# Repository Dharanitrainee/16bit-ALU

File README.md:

<h1>16-bit ALU with ESP32 Control Unit</h1>

<p>This project implements a 16-bit Arithmetic Logic Unit (ALU) using TTL (74 series) digital integrated circuits. The control unit is built using an ESP32 microcontroller, enhancing functionality with a user-friendly interface via an OLED display and a rotary encoder for selecting operations.</p>

<blockquote>
  <strong>Disclaimer</strong>: This is my first PCB design, and there may be flaws.This may be the worls worst ALU!. Any feedback or suggestions for improvement are welcome.
</blockquote>

<h2>Features</h2>

<ul>
  <li><strong>Arithmetic Operations</strong>: Addition, Subtraction, Increment, Decrement.</li>
  <li><strong>Logical Operations</strong>: AND, OR, XOR, NOT.</li>
  <li><strong>User Interface</strong>: An OLED display shows the current operation, and a rotary encoder allows for easy selection of operations.</li>
  <li><strong>Control Mechanism</strong>: ESP32 provides control signals and manages data flow within the ALU using shift registers.</li>
</ul>

<h2>Components Used</h2>

<ul>
  <li><strong>TTL ICs (74 series)</strong> for logic implementation</li>
  <li><strong>ESP32 microcontroller</strong> for control signals</li>
  <li><strong>OLED Display (SH1106)</strong> for displaying selected operation and result</li>
  <li><strong>Rotary Encoder (KY-040)</strong> for operation selection</li>
  <li><strong>Shift Registers (74HC595)</strong> for handling input/output</li>
</ul>

<h2>Project Structure</h2>

<ul>
  <li><code>main_code.ino</code>: The primary Arduino code for the ESP32, managing the control signals, encoder input, OLED output, and ALU operations.</li>
  <li><code>images/</code>: Contains bitmaps for icons representing each operation.</li>
  <li><code>README.md</code>: Project documentation.</li>
</ul>

<h2>How It Works</h2>

<ol>
  <li><strong>Control Unit</strong>: The ESP32 microcontroller generates control signals based on user input from the rotary encoder. The OLED screen displays the current operation, input values, and results.</li>
  <li><strong>ALU Operations</strong>: The ALU performs selected operations on 16-bit data, interfaced via shift registers.</li>
  <li><strong>Result Display</strong>: The result of the operation is shown on the OLED display.</li>
</ol>

<h2>Setup and Usage</h2>

<ol>
  <li>Connect the ESP32 to the OLED display and rotary encoder.</li>
  <li>Interface the shift registers with TTL ICs to implement the 16-bit ALU logic.</li>
  <li>Load the Arduino code onto the ESP32.</li>
  <li>Use the rotary encoder to select the desired operation and input values, then view the result on the OLED display.</li>
</ol>

<h2>Future Improvements</h2>

<ul>
  <li>Expand operations to include multiplication and division.</li>
  <li>Optimize the control signal generation for improved speed and accuracy.</li>
  <li>Add support for additional user inputs or controls to expand functionality.</li>
</ul>

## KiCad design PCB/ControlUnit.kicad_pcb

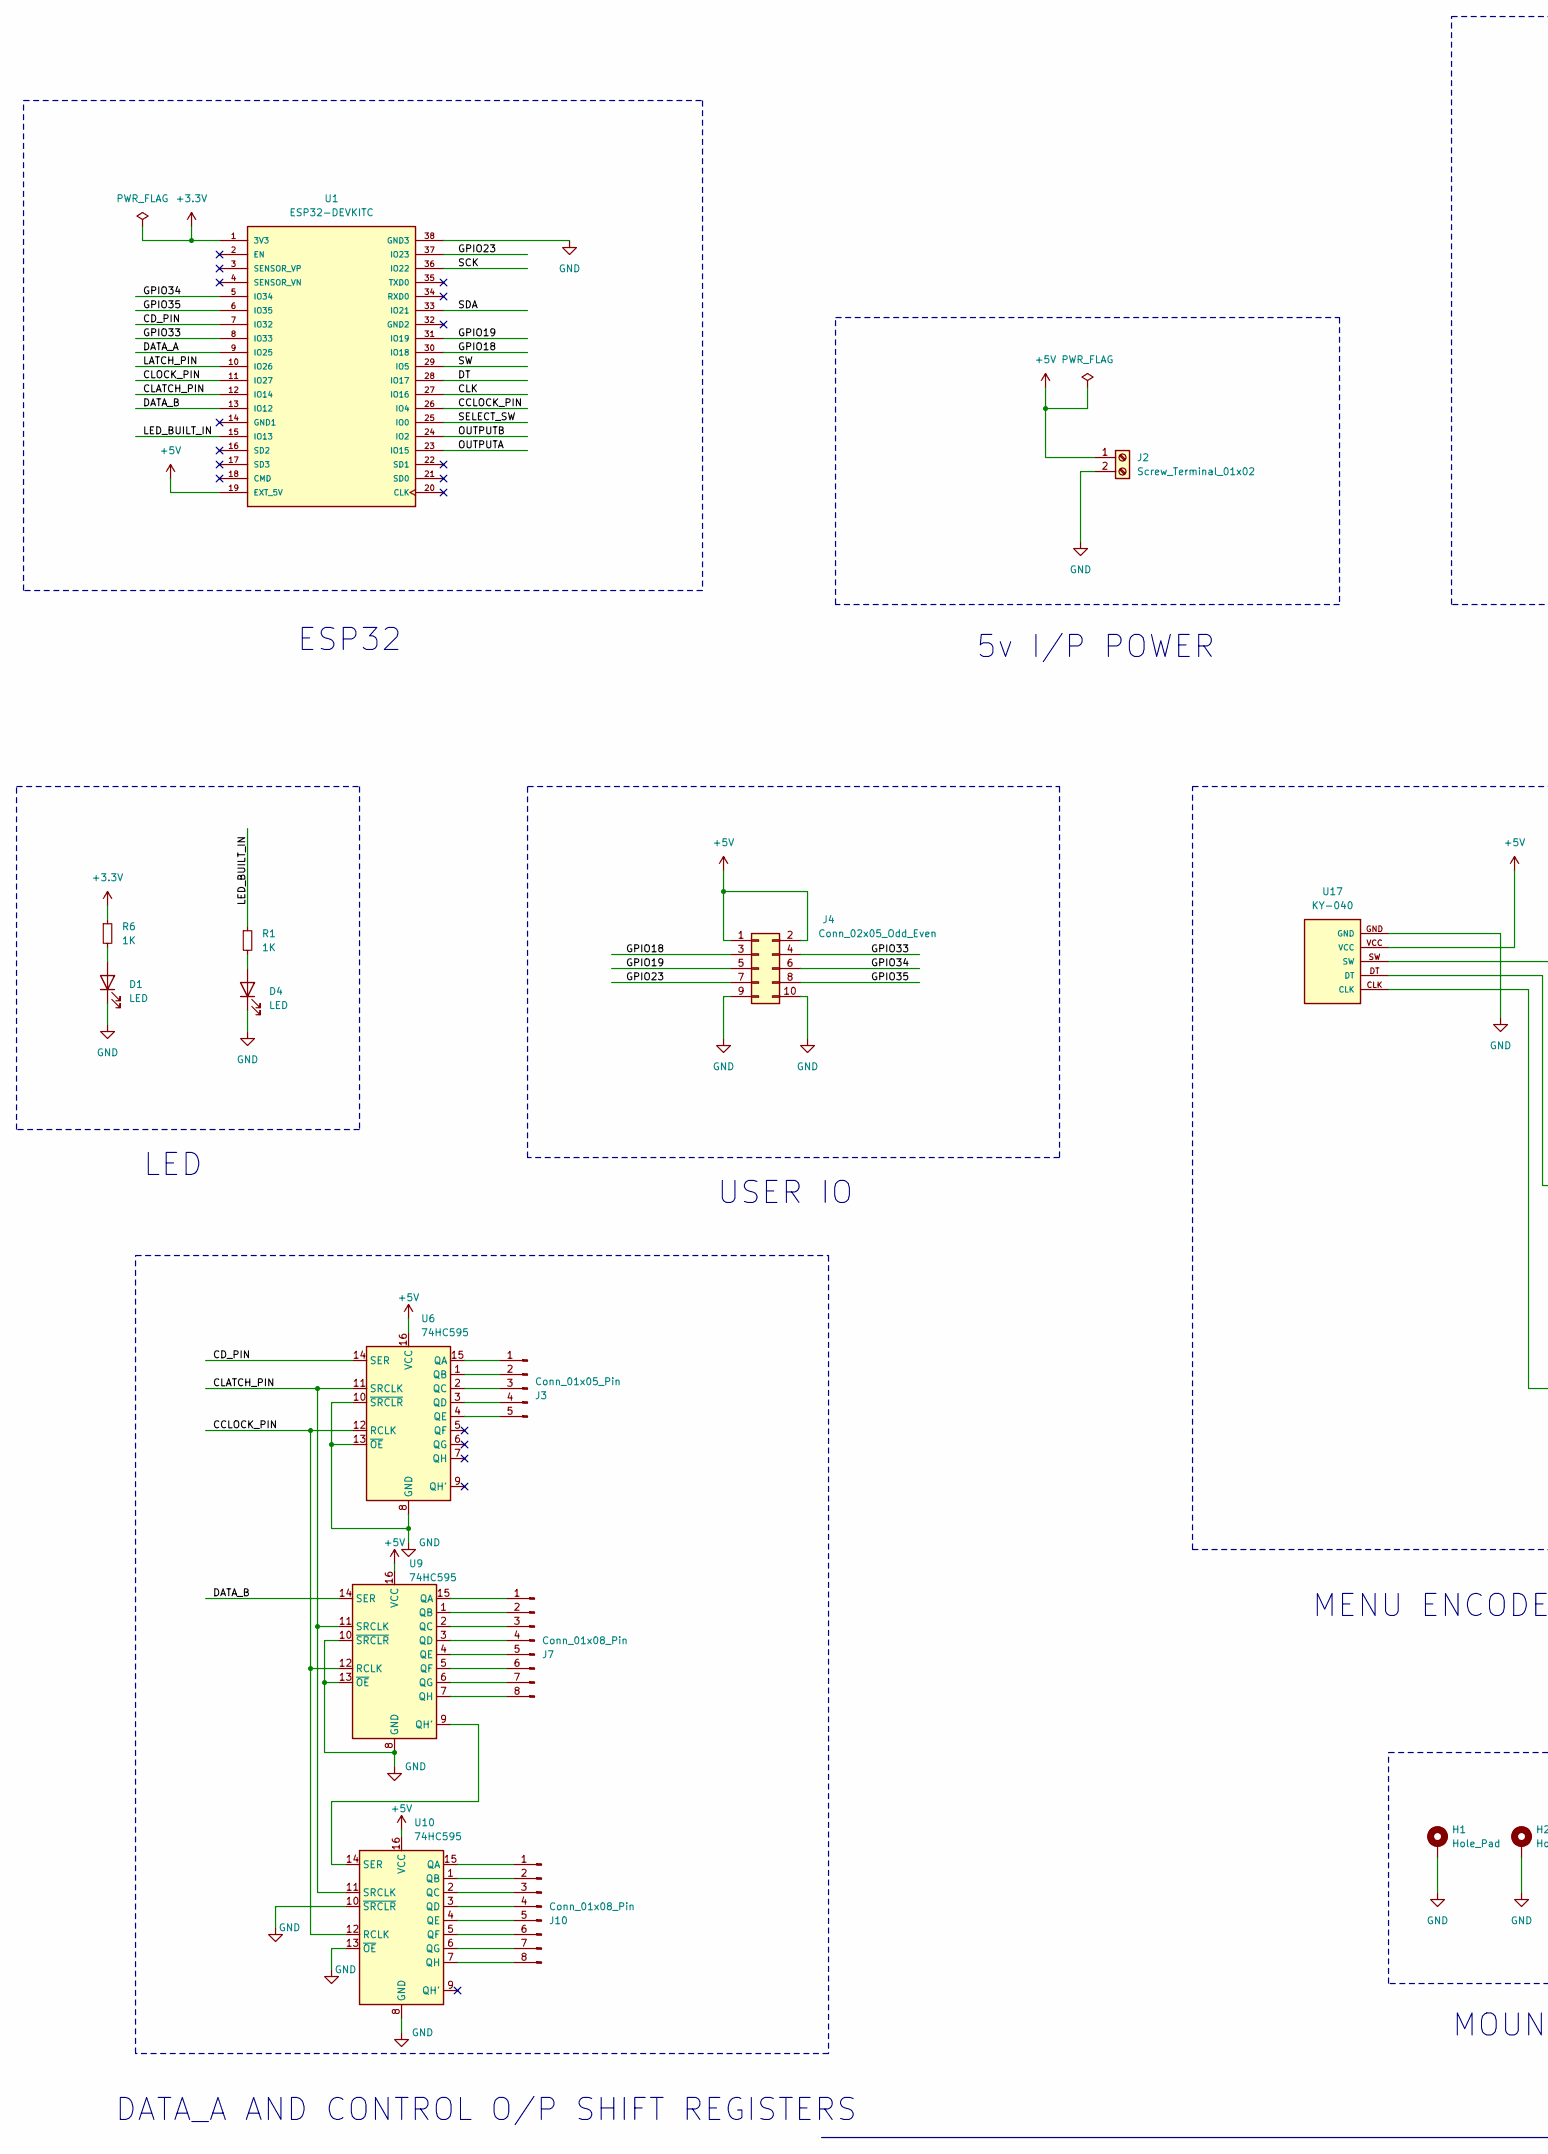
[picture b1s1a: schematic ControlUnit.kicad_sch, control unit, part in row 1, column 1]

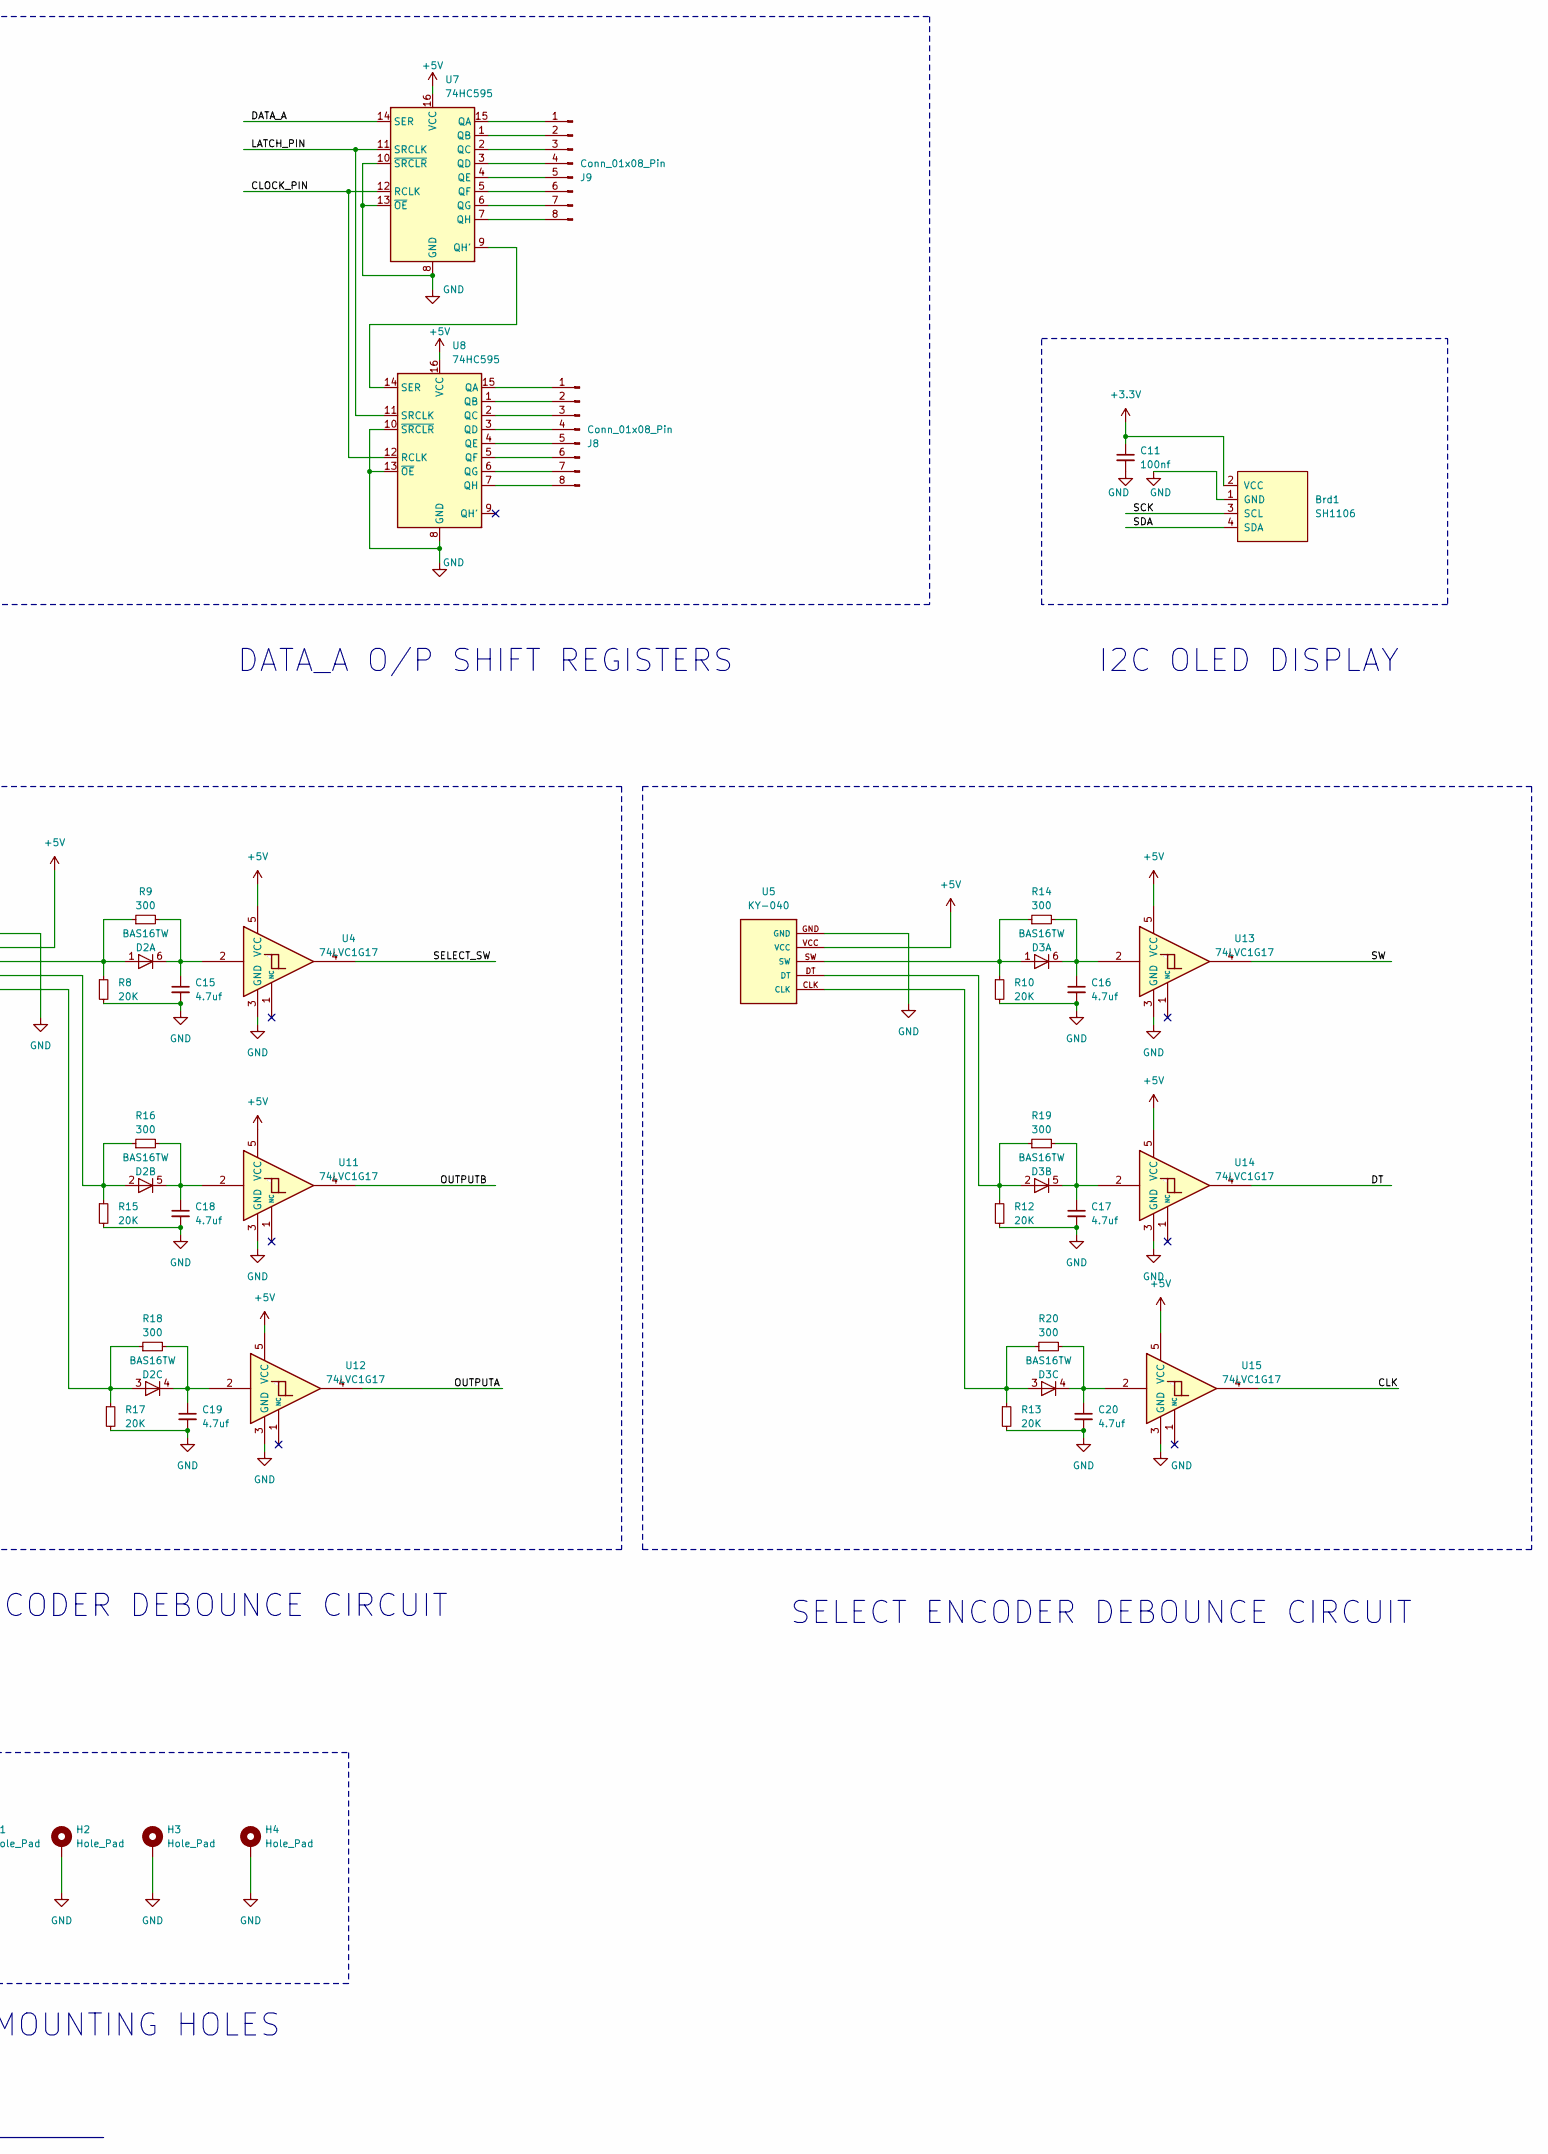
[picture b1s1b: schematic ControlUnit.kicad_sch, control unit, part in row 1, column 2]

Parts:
Brd1: SH1106; 128x64OLED
C11: 100nf; C_0402_1005Metric_Pad0.74x0.62mm_HandSolder
C15, C16, C17, C18, C19, C20: 4.7uf; C_0805_2012Metric_Pad1.18x1.45mm_HandSolder
D1, D4: LED; LED_0603_1608Metric_Pad1.05x0.95mm_HandSolder
D2, D3: BAS16TW; SOT-363_SC-70-6
H1, H2, H3, H4: Hole_Pad; MountingHole_3.2mm_M3_Pad_Via
J2: Screw_Terminal_01x02; TerminalBlock_Phoenix_MKDS-1,5-2-5.08_1x02_P5.08mm_Horizont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
J3: Conn_01x05_Pin; PinHeader_1x05_P1.00mm_Vertical
J4: Conn_02x05_Odd_Even; PinHeader_2x05_P1.00mm_Vertical
J7, J8, J9, J10: Conn_01x08_Pin; PinHeader_1x08_P1.00mm_Vertical
R1, R6: 1K; R_0402_1005Metric_Pad0.72x0.64mm_HandSolder
R8, R10, R12, R13, R15, R17: 20K; R_0402_1005Metric_Pad0.72x0.64mm_HandSolder
R9, R14, R16, R18, R19, R20: 300; R_0402_1005Metric_Pad0.72x0.64mm_HandSolder
U1: ESP32-DEVKITC; MODULE_ESP32-DEVKITC; PARTREV N/A
U4, U11, U12, U13, U14, U15: 74LVC1G17; SOT23-5
U5, U17: KY-040; KY-040-PORT
U6, U7, U8, U9, U10: 74HC595; DIP-16_W10.16mm_LongPads

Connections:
+3.3V: Brd1.2 (VCC), C11.1, R6.1, U1.1 (3V3)
+5V: J2.1, J4.1, J4.2, U1.19 (EXT_5V), U4.5 (VCC), U5.VCC, U6.16 (VCC), U7.16 (VCC), U8.16 (VCC), U9.16 (VCC), U10.16 (VCC), U11.5 (VCC), U12.5 (VCC), U13.5 (VCC), U14.5 (VCC), U15.5 (VCC), U17.VCC
/CCLOCK_PIN: U1.26 (IO4), U6.12 (RCLK), U9.12 (RCLK), U10.12 (RCLK)
/CD_PIN: U1.7 (IO32), U6.14 (SER)
/CLATCH_PIN: U1.12 (IO14), U6.11 (SRCLK), U9.11 (SRCLK), U10.11 (SRCLK)
/CLK: U1.27 (IO16), U15.4
/CLOCK_PIN: U1.11 (IO27), U7.12 (RCLK), U8.12 (RCLK)
/DATA_A: U1.9 (IO25), U7.14 (SER)
/DATA_B: U1.13 (IO12), U9.14 (SER)
/DT: U1.28 (IO17), U14.4
/GPIO18: J4.3, U1.30 (IO18)
/GPIO19: J4.5, U1.31 (IO19)
/GPIO23: J4.7, U1.37 (IO23)
/GPIO33: J4.4, U1.8 (IO33)
/GPIO34: J4.6, U1.5 (IO34)
/GPIO35: J4.8, U1.6 (IO35)
/LATCH_PIN: U1.10 (IO26), U7.11 (SRCLK), U8.11 (SRCLK)
/LED_BUILT_IN: R1.1, U1.15 (IO13)
/OUTPUTA: U1.23 (IO15), U12.4
/OUTPUTB: U1.24 (IO2), U11.4
/SCK: Brd1.3 (SCL), U1.36 (IO22)
/SDA: Brd1.4 (SDA), U1.33 (IO21)
/SELECT_SW: U1.25 (IO0), U4.4
/SW: U1.29 (IO5), U13.4
GND: Brd1.1 (GND), C11.2, C15.2, C16.2, C17.2, C18.2, C19.2, C20.2, D1.1 (K), D4.1 (K), H1.1, H2.1, H3.1, H4.1, J2.2, J4.9, J4.10, R8.2, R10.2, R12.2, R13.2, R15.2, R17.2, U1.38 (GND3), U4.3 (GND), U5.GND, U6.8 (GND), U6.10 (~SRCLR), U6.13 (~OE), U7.8 (GND), U7.10 (~SRCLR), U7.13 (~OE), U8.8 (GND), U8.10 (~SRCLR), U8.13 (~OE), U9.8 (GND), U9.10 (~SRCLR), U9.13 (~OE), U10.8 (GND), U10.10 (~SRCLR), U10.13 (~OE), U11.3 (GND), U12.3 (GND), U13.3 (GND), U14.3 (GND), U15.3 (GND), U17.GND
unnamed: D1.2 (A), R6.2
unnamed: D2.1 (A), R8.1, R9.1, U17.SW
unnamed: C15.1, D2.6 (K), R9.2, U4.2
unnamed: D2.2 (A), R15.1, R16.1, U17.DT
unnamed: C18.1, D2.5 (K), R16.2, U11.2
unnamed: D2.3 (A), R17.1, R18.1, U17.CLK
unnamed: C19.1, D2.4 (K), R18.2, U12.2
unnamed: D3.1 (A), R10.1, R14.1, U5.SW
unnamed: C16.1, D3.6 (K), R14.2, U13.2
unnamed: D3.2 (A), R12.1, R19.1, U5.DT
unnamed: C17.1, D3.5 (K), R19.2, U14.2
unnamed: D3.3 (A), R13.1, R20.1, U5.CLK
unnamed: C20.1, D3.4 (K), R20.2, U15.2
unnamed: D4.2 (A), R1.2
unnamed: J3.1, U6.15 (QA)
unnamed: J3.2, U6.1 (QB)
unnamed: J3.3, U6.2 (QC)
unnamed: J3.4, U6.3 (QD)
unnamed: J3.5, U6.4 (QE)
unnamed: J7.1, U9.15 (QA)
unnamed: J7.2, U9.1 (QB)
unnamed: J7.3, U9.2 (QC)
unnamed: J7.4, U9.3 (QD)
unnamed: J7.5, U9.4 (QE)
unnamed: J7.6, U9.5 (QF)
unnamed: J7.7, U9.6 (QG)
unnamed: J7.8, U9.7 (QH)
unnamed: J8.1, U8.15 (QA)
unnamed: J8.2, U8.1 (QB)
unnamed: J8.3, U8.2 (QC)
unnamed: J8.4, U8.3 (QD)
unnamed: J8.5, U8.4 (QE)
unnamed: J8.6, U8.5 (QF)
unnamed: J8.7, U8.6 (QG)
unnamed: J8.8, U8.7 (QH)
unnamed: J9.1, U7.15 (QA)
unnamed: J9.2, U7.1 (QB)
unnamed: J9.3, U7.2 (QC)
unnamed: J9.4, U7.3 (QD)
unnamed: J9.5, U7.4 (QE)
unnamed: J9.6, U7.5 (QF)
unnamed: J9.7, U7.6 (QG)
unnamed: J9.8, U7.7 (QH)
unnamed: J10.1, U10.15 (QA)
unnamed: J10.2, U10.1 (QB)
unnamed: J10.3, U10.2 (QC)
unnamed: J10.4, U10.3 (QD)
unnamed: J10.5, U10.4 (QE)
unnamed: J10.6, U10.5 (QF)
unnamed: J10.7, U10.6 (QG)
unnamed: J10.8, U10.7 (QH)
unnamed: U7.9 (QH'), U8.14 (SER)
unnamed: U9.9 (QH'), U10.14 (SER)

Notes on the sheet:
5v I/P POWER
DATA_A O/P SHIFT REGISTERS
USER IO
SELECT ENCODER DEBOUNCE CIRCUIT
I2C OLED DISPLAY
DATA_A AND CONTROL O/P SHIFT REGISTERS
ESP32
LED
MENU ENCODER DEBOUNCE CIRCUIT
MOUNTING HOLES

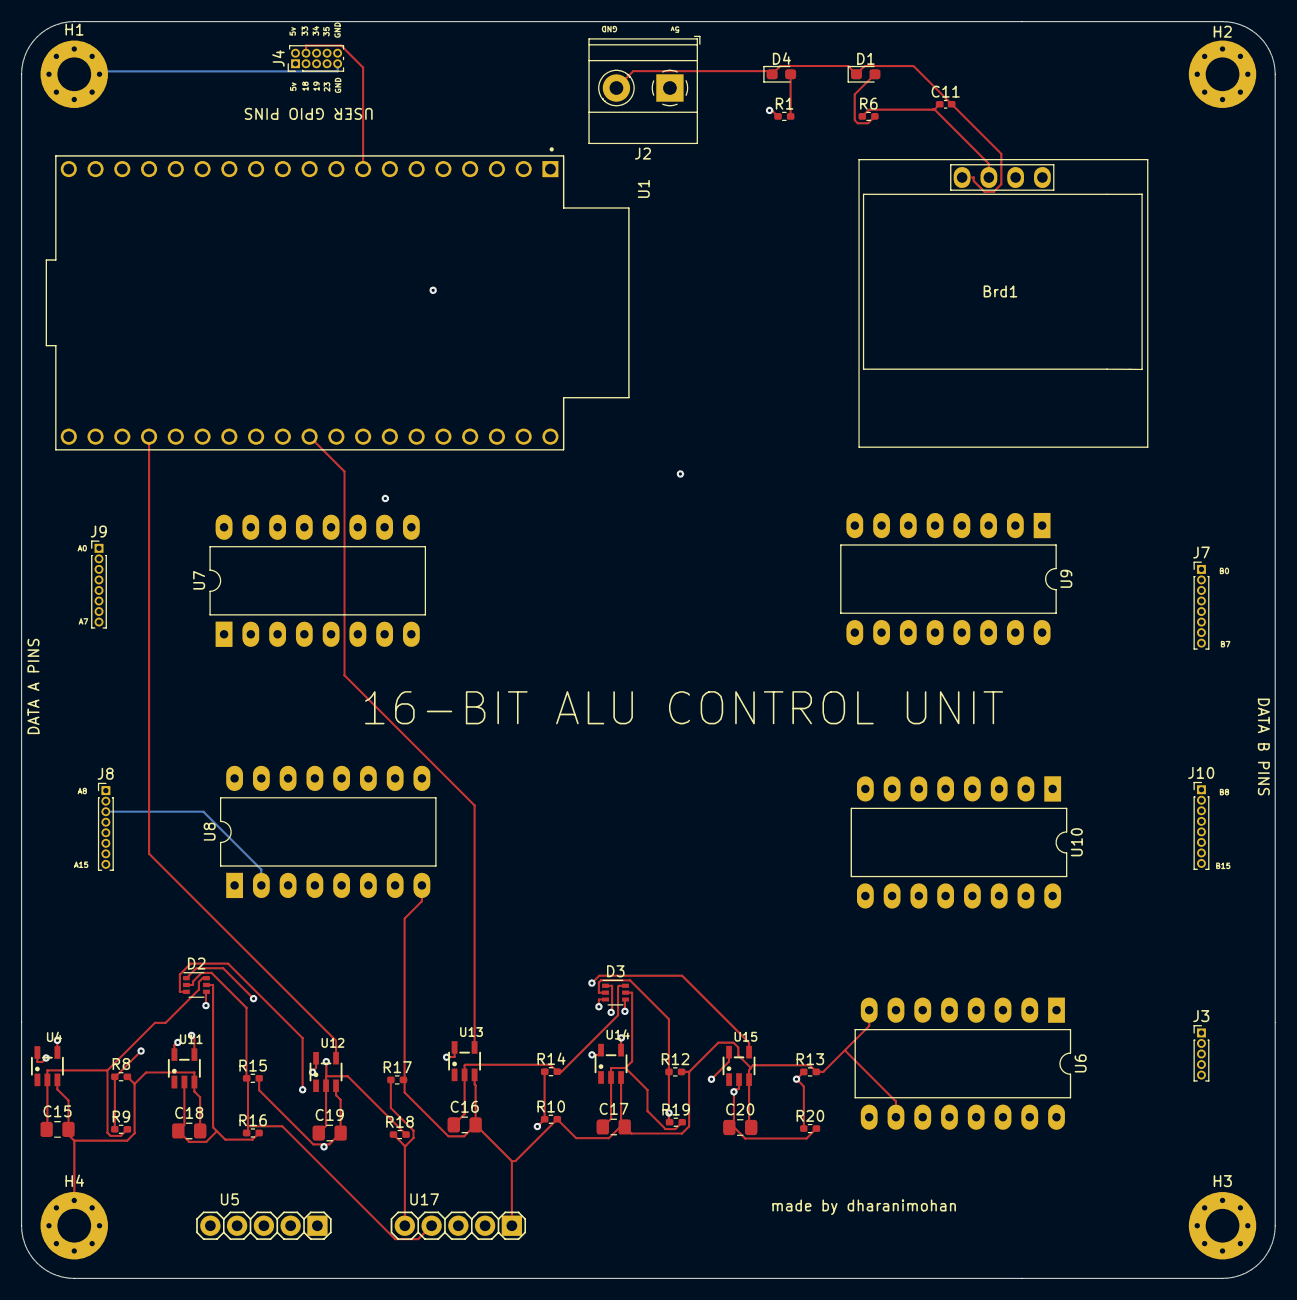
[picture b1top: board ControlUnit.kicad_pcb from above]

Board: 4 copper layers, 119.0 x 119.3 mm, 51 parts (0 on the bottom side), 78 nets.

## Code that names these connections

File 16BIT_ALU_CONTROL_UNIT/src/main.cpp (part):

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};

//Menu encoder pins
#define outputA 15 
#define outputB 2
#define select_sw 0

//Value select encoder pins
#define clk 16
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
//Data shift register pins
#define DATA_PIN  25 
#define LATCH_PIN 26  
#define CLOCK_PIN 27 
#define DATAB_PIN 12

//controlbits shift register pins
#define CD_PIN 32
#define CLATCH_PIN 14
#define CCLOCK_PIN 4


int item_selected = 0;
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int value_select_clicked = 0;

volatile int encoderValue;
volatile long data_a = 0,data_b = 0;

int PreviousCLK;
int PreviousDATA;
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
void writeRegistersA(int DATA_A)
{
  digitalWrite(LATCH_PIN,LOW);
  shiftOut(DATA_PIN,CLOCK_PIN,MSBFIRST,DATA_A);
  digitalWrite(LATCH_PIN, HIGH);
  digitalWrite(LATCH_PIN, LOW);
}

void writeRegistersAndControl(int DATA_B, int controlSignal) {
  digitalWrite(CLATCH_PIN, LOW);
  shiftOut(DATAB_PIN, CCLOCK_PIN, LSBFIRST, DATA_B);
  shiftOut(CD_PIN, CCLOCK_PIN, MSBFIRST, controlSignal);
  digitalWrite(CLATCH_PIN, HIGH);
  digitalWrite(CLATCH_PIN, LOW);
}

void reset()
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    } else if (current_screen == 2) {
      current_screen = 3;
      if(control_signals[item_selected+1] == INCREMENT_A_SIGNAL){
      data_b = 0;
      }
      else if(control_signals[item_selected+1] == DECREMENT_A_SIGNAL){
      data_b = 1;
      }
      else{
      data_b = encoderValue;}
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
void setup() {
  Serial.begin(115200);
  pinMode(outputA, INPUT_PULLUP);
  pinMode(outputB, INPUT_PULLUP);
  pinMode(select_sw, INPUT_PULLUP);
  pinMode(DATA_PIN, OUTPUT);
  pinMode(CLOCK_PIN, OUTPUT);
  pinMode(LATCH_PIN, OUTPUT);
  pinMode(clk, INPUT_PULLUP);
  pinMode(dt, INPUT_PULLUP);
  pinMode(sw, INPUT_PULLUP);
  pinMode(CD_PIN,OUTPUT);
  pinMode(CLATCH_PIN,OUTPUT);
  pinMode(CCLOCK_PIN,OUTPUT);
  pinMode(DATAB_PIN,OUTPUT);

  attachInterrupt(digitalPinToInterrupt(outputA), updateEncoder, CHANGE);
  attachInterrupt(digitalPinToInterrupt(outputB), updateEncoder, CHANGE);
  attachInterrupt(digitalPinToInterrupt(select_sw), select_ISR, CHANGE);
  attachInterrupt(digitalPinToInterrupt(clk), encoder_ISR, CHANGE);
  attachInterrupt(digitalPinToInterrupt(dt), encoder_ISR, CHANGE);
  attachInterrupt(digitalPinToInterrupt(sw), value_select_ISR, CHANGE);
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
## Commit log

2023-12-23 main.cpp
2024-04-28 added pcb.txt
2024-11-10 README.md
